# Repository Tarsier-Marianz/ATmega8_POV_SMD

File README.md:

# ATmega8_POV_SMD

Surface mounted version of ATmega8_POV, persistence-of-vision (POV) display with ATmega8 microcontroller

## Thanks

[KiCad IDE](http://kicad-pcb.org/) - for letting me use a free software in designing PCB.

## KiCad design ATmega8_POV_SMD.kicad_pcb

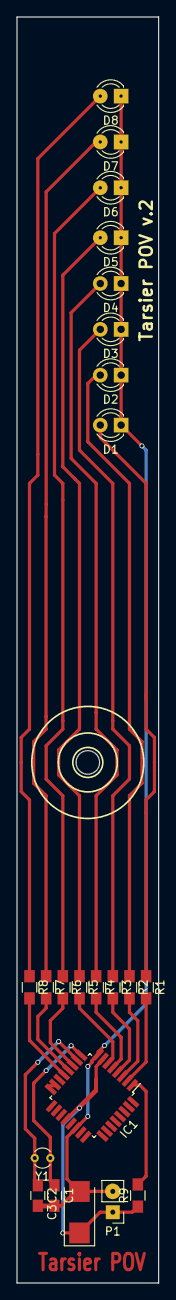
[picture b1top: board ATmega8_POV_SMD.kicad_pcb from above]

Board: 2 copper layers, 17.3 x 154.4 mm, 23 parts (0 on the bottom side), 21 nets.

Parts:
C1, C2: 22pF; C_0805_HandSoldering
C3: 4.7uF; CP_Tantalum_Case-C_EIA-6032-28_Reflow
D1, D2, D3, D4, D5, D6, D7, D8: LED; LED_D3.0mm
IC1: ATMEGA8-P; TQFP-32_7x7mm_Pitch0.8mm
P1: CONN_01X02; Pin_Header_Straight_1x02_Pitch2.54mm
R1, R2, R3, R4, R5, R6, R7, R8: 1K; R_0805_HandSoldering
R9: 10K; R_0805_HandSoldering
Y1: Crystal_Small; Crystal_C26-LF_d2.1mm_l6.5mm_Vertical

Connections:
/D0: IC1.2, R1.2
/D1: IC1.3, R2.2
/D2: IC1.4, R3.2
/D3: IC1.5, R4.2
/D4: IC1.6, R5.2
/D5: IC1.11, R6.2
/D6: IC1.12, R7.2
/D7: IC1.13, R8.2
GND: C1.2, C2.2, C3.2, D1.1, D2.1, D3.1, D4.1, D5.1, D6.1, D7.1, D8.1, IC1.8, IC1.22, P1.2
unnamed: C1.1, IC1.9, Y1.1
unnamed: C2.1, IC1.10, Y1.2
unnamed: D1.2, R1.1
unnamed: D2.2, R2.1
unnamed: D3.2, R3.1
unnamed: D4.2, R4.1
unnamed: D5.2, R5.1
unnamed: D6.2, R6.1
unnamed: D7.2, R7.1
unnamed: D8.2, R8.1
unnamed: IC1.1, R9.2
VCC: C3.1, IC1.7, IC1.20, P1.1, R9.1

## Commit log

2018-03-23 *changed footprints of every schematic components
2018-03-23 *generating new netlist from new components footprint
2018-03-23 ~aligning pcb components
2018-03-24 ~finalized pcb layout
2018-03-24 +readme image prototype board 3D view
2018-03-26 >moving resistors near to IC
2018-03-26 *readme with v2 of prototype board
2018-04-05 :deciduous_tree: duh!
2018-04-10 *fix 3D view exception
